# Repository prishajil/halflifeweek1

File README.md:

# Starbie Project!

### These are my components in Schematic Editor! 

### This is what I was able to get my PCB to. I added some cute space-themed customizations through the Image Editor! Not exactly sure how they're going to show up on my actual, physical Starbie, though. Haha

### How I made it
### Why I made it
### How to assemble it
### How to flash firmware
### BOM table:

| Item | amount | cost (ea.) | Link |
| :--- | :---: | :---: | :--- |
| XIAO ESP32 C3 | 1 | 4.49 | https://www.seeedstudio.com/Seeed-Studio-XIAO-ESP32C3-Tape-Reel-p-6471.html |
| 0.96 OLED | 1 | 2.95 | https://www.elexp.com/products/0-96-oled-i2c-iic-display-module-oled-screen-board-1 |
| MPU6050 | 1 | 1.96 | https://electropeak.com/gyro-accelerometer-gy521-mpu6050 |
| DHT11 | 1 | 2.49 | https://www.addicore.com/products/dht11-temperature-and-humidity-sensor |
| MX Key Switches (Need 4 pcs, still $5.95) | 4 | 1.49 ea. | https://www.adafruit.com/product/6022 |
| Keycaps (Need to buy only 1, but it comes with 4!) | 4 | 1.50 | https://mechanicalkeyboards.com/products/tai-hao-4-key-tpr-blank-rubber-keycap-set-neon-pink-row-2 |
| 10k Resistor | 1 | 0.10 | https://www.addicore.com/products/10k-ohm-1-4w-precision-resistor?_su_rec=R76qX_fZJZL6g3kXQINdC2Rw67UEmnbBfnwfI36LsI1Um_-5Z9x3vy3GbkCu6m6hvEVmPTtMlVWTaI8144FtxqWG_-RjDtD_wKRwhifkBwP9B5s61qVdSQMfbkeva0_1WzXbrIIXdur733hKR8bECv9v3o7j1_ihFvgluzNX25-XSPNPpq994dqBUnovN5511N4tKpvN4SggyRJ3RLKe9Buc3U3A19iC1lw_KFx1o9nsoBNC1e-ZsTrqYsLOoFkxR6oAUUnFYd5cZSLrwR56j-XQRvGrQ-gc61vpdBB_2H08SoJiS-1-k-2mMHKAQyTskb3ElBKS7OfiGWUOgeamLA&_su_rec_id=64825e44-72a5-4770-87e6-e58860e8f016-1791772037 |
| PCB | 1 | $6.30 | https://www.jlcpcb.com/ |
| | | | |
| Total (each kit) | 1 | 25.84 | |

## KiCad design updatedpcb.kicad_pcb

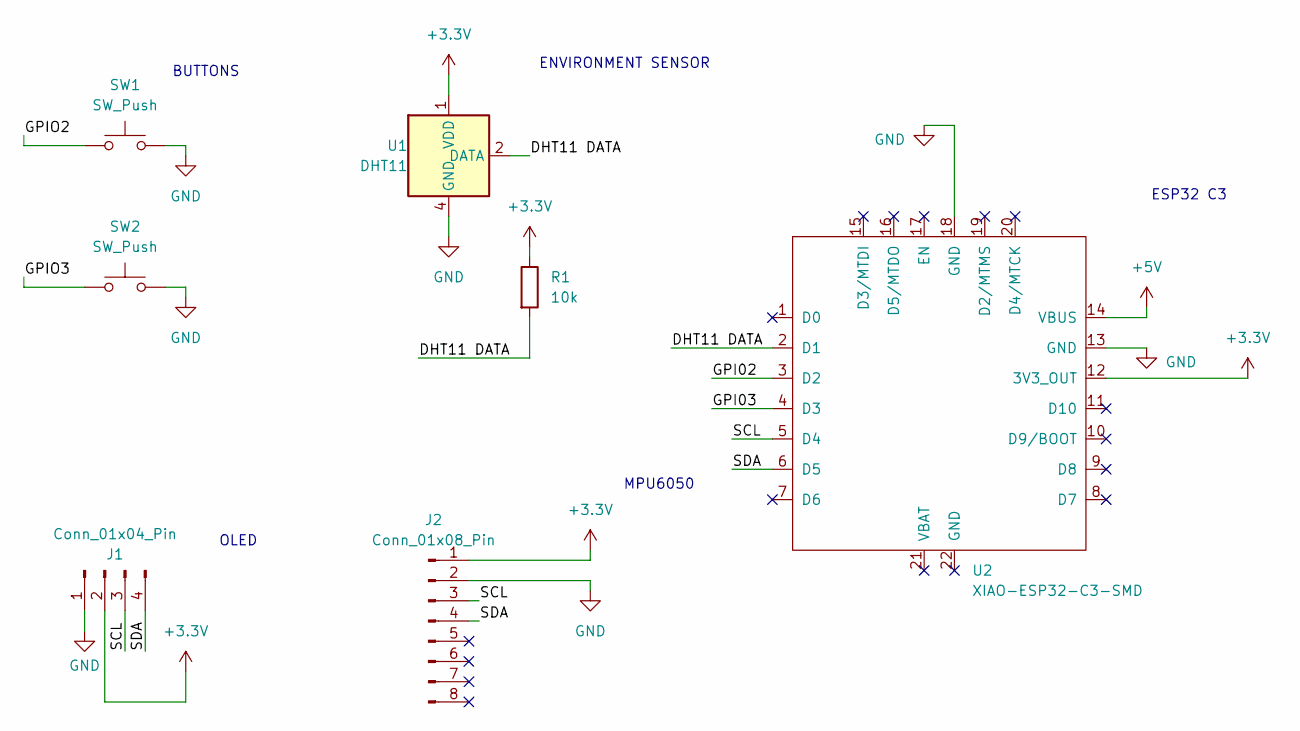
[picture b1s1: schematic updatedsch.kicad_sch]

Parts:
J1: Conn_01x04_Pin; Display_128x64_096_I2C
J2: Conn_01x08_Pin; PinHeader_1x08_P2.54mm_Vertical
R1: 10k; R_Axial_DIN0204_L3.6mm_D1.6mm_P7.62mm_Horizontal
SW1, SW2: SW_Push; SW_Cherry_MX_1.00u_PCB
U1: DHT11; Aosong_DHT11_5.5x12.0_P2.54mm
U2: XIAO-ESP32-C3-SMD

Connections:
+3.3V: J1.2, J2.1, R1.1, U1.1 (VDD), U2.12 (3V3_OUT)
+5V: U2.14 (VBUS)
/DHT11 DATA: R1.2, U1.2 (DATA), U2.2 (D1)
/GPI02: U2.3 (D2)
/GPI03: U2.4 (D3)
/GPIO2: SW1.1
/GPIO3: SW2.1
/SCL: J1.3, J2.3, U2.5 (D4)
/SDA: J1.4, J2.4, U2.6 (D5)
GND: J1.1, J2.2, SW1.2, SW2.2, U1.4 (GND), U2.13 (GND), U2.18 (GND)

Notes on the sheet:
BUTTONS
OLED
ESP32 C3
ENVIRONMENT SENSOR
MPU6050

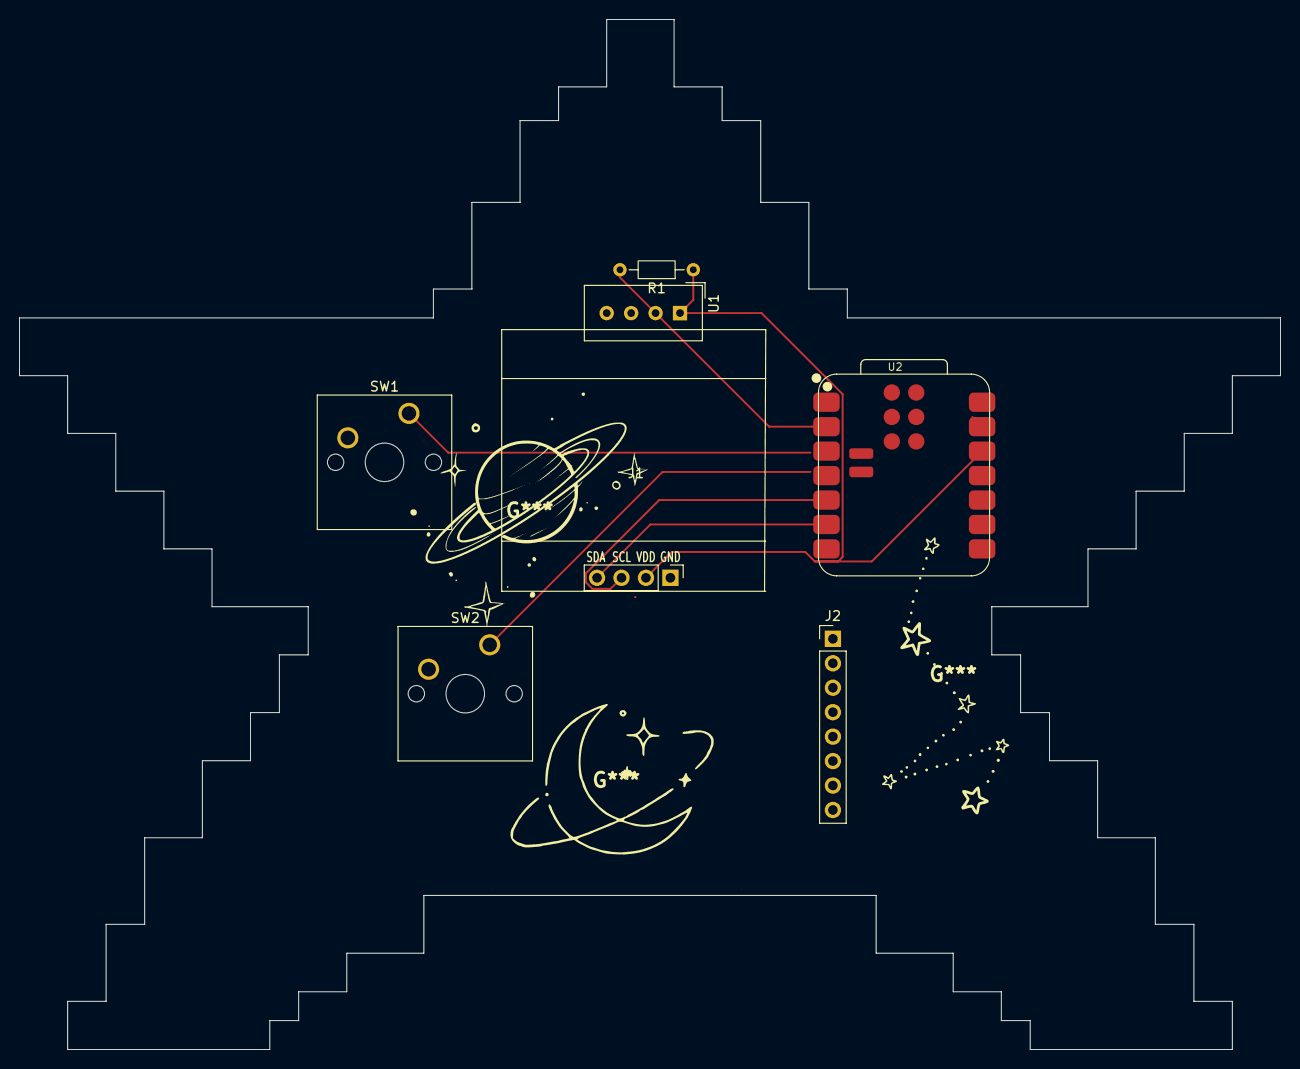
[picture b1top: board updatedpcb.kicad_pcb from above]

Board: 2 copper layers, 131.0 x 107.0 mm, 7 parts (0 on the bottom side), 5 nets.
